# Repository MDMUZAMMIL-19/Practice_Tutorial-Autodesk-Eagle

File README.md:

# Practice_Tutorial-Autodesk-Eagle
This repository contains a collection of PCB design projects that I have completed as part of my learning journey using softwares like Autodesk Eagle, Fusion360 and EasyEDA. These projects are based on various tutorials I followed to learn PCB Design.

This repository includes the following:

Project Folders: Each project has its own folder containing all relevant files.

Schematics: .sch files for schematic diagrams and their Pdf.

Board Layouts: .brd files for PCB layouts and their Pdf.

Gerber Files: Generated Gerber files for manufacturing.

Bill of Materials (BOM): Lists of components used in each project.

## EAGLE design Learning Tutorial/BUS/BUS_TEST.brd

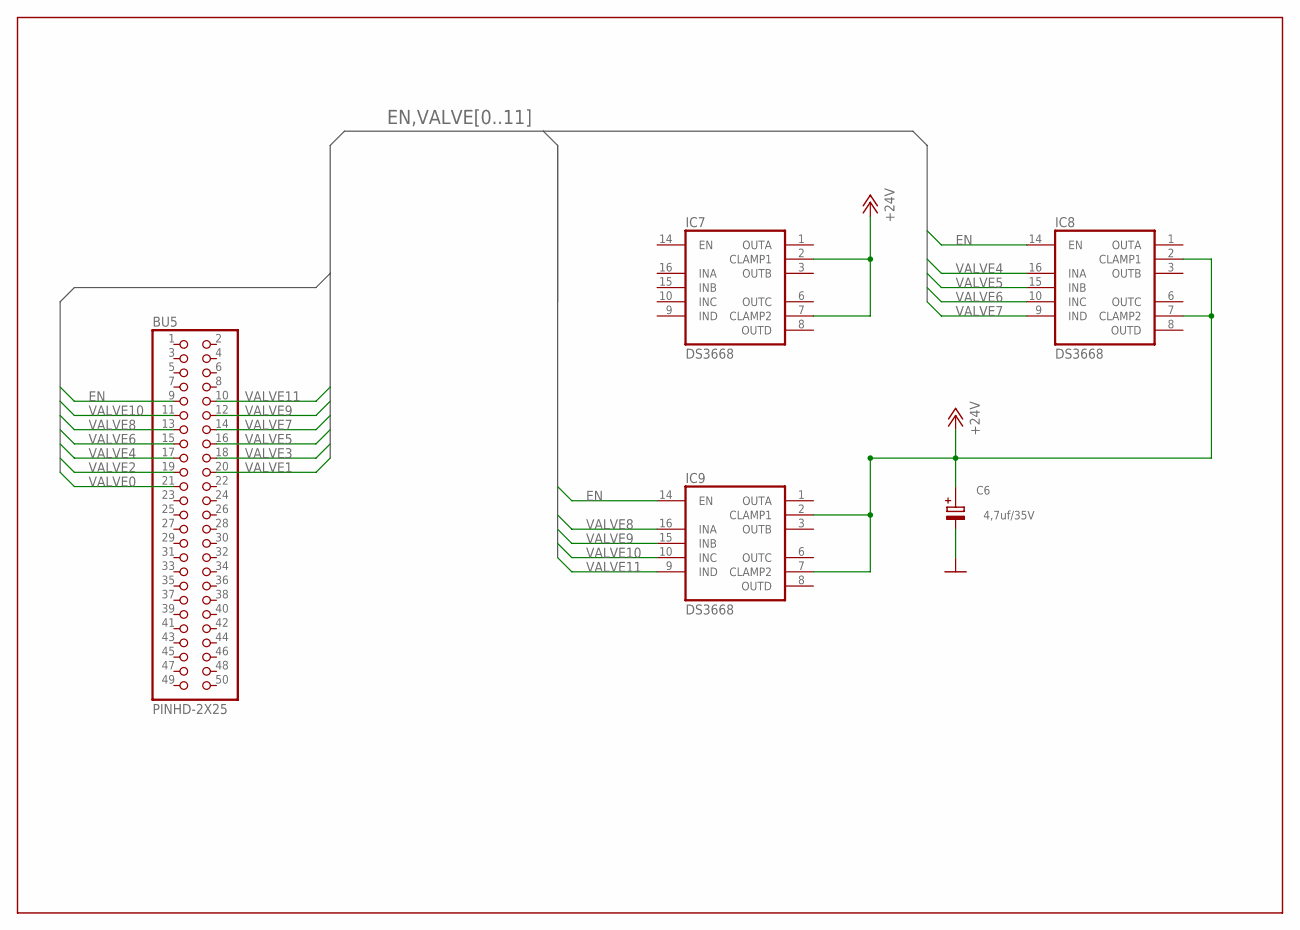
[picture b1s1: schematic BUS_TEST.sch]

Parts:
BU5: PINHD-2X25; 2X25
C6: 4,7uf/35V; E2,5-5
IC7, IC8, IC9: DS3668; DIL-16

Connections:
+24V: C6.+, IC7.2 (CLAMP1), IC7.7 (CLAMP2), IC8.2 (CLAMP1), IC8.7 (CLAMP2), IC9.2 (CLAMP1), IC9.7 (CLAMP2)
EN: BU5.9, IC8.14 (EN), IC9.14 (EN)
GND: C6.-
VALVE0: BU5.21
VALVE1: BU5.20
VALVE2: BU5.19
VALVE3: BU5.18
VALVE4: BU5.17, IC8.16 (INA)
VALVE5: BU5.16, IC8.15 (INB)
VALVE6: BU5.15, IC8.10 (INC)
VALVE7: BU5.14, IC8.9 (IND)
VALVE8: BU5.13, IC9.16 (INA)
VALVE9: BU5.12, IC9.15 (INB)
VALVE10: BU5.11, IC9.10 (INC)
VALVE11: BU5.10, IC9.9 (IND)
VCC: IC7.11 (VCC), IC8.11 (VCC), IC9.11 (VCC)
VSS: IC7.4 (VSS), IC7.5 (VSS), IC7.12 (VSS), IC7.13 (VSS), IC8.4 (VSS), IC8.5 (VSS), IC8.12 (VSS), IC8.13 (VSS), IC9.4 (VSS), IC9.5 (VSS), IC9.12 (VSS), IC9.13 (VSS)

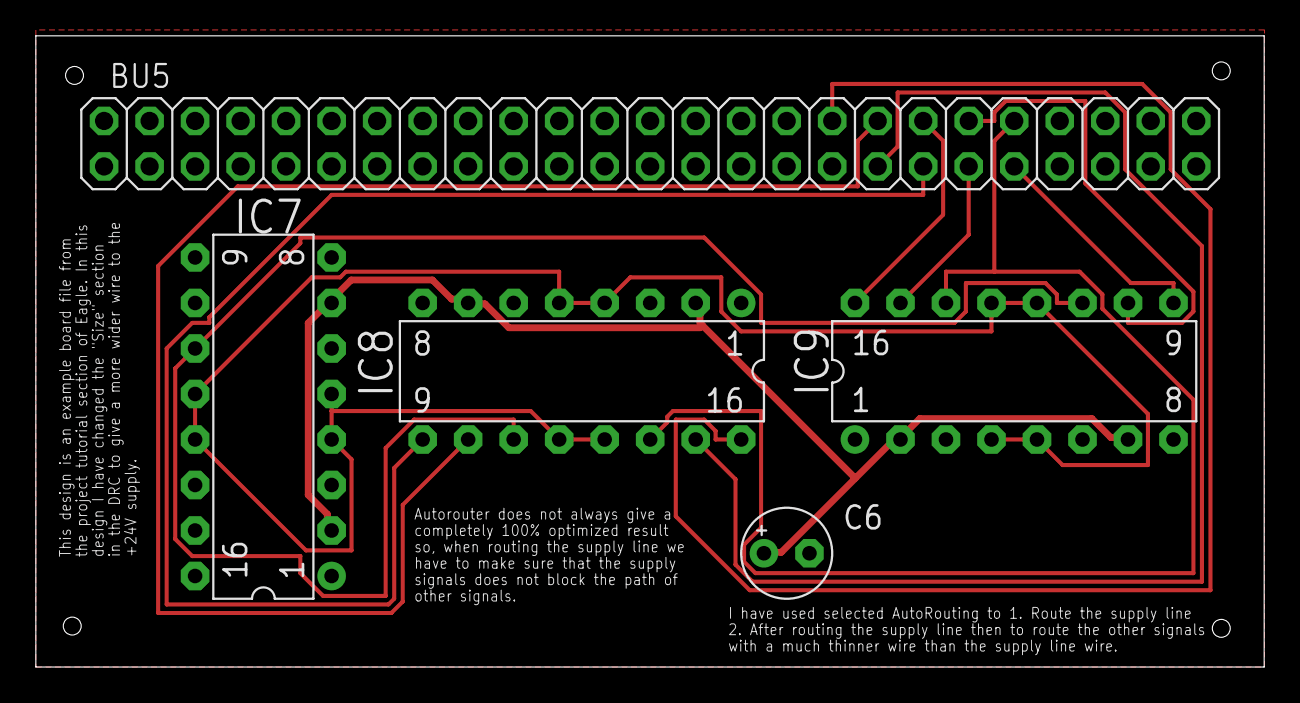
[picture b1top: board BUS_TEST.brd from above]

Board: 2 copper layers, 68.6 x 35.2 mm, 5 parts (0 on the bottom side), 12 nets.

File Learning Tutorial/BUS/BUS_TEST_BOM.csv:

Qty,Value,Device,Package,Parts
1,"4,7uf/35V",E2-5@1,"E2,5-5",C6
3,DS3668,DS3668,DIL-16,"IC7, IC8, IC9"
1,PINHD-2X25,PINHD-2X25,2X25,BU5
,,,,

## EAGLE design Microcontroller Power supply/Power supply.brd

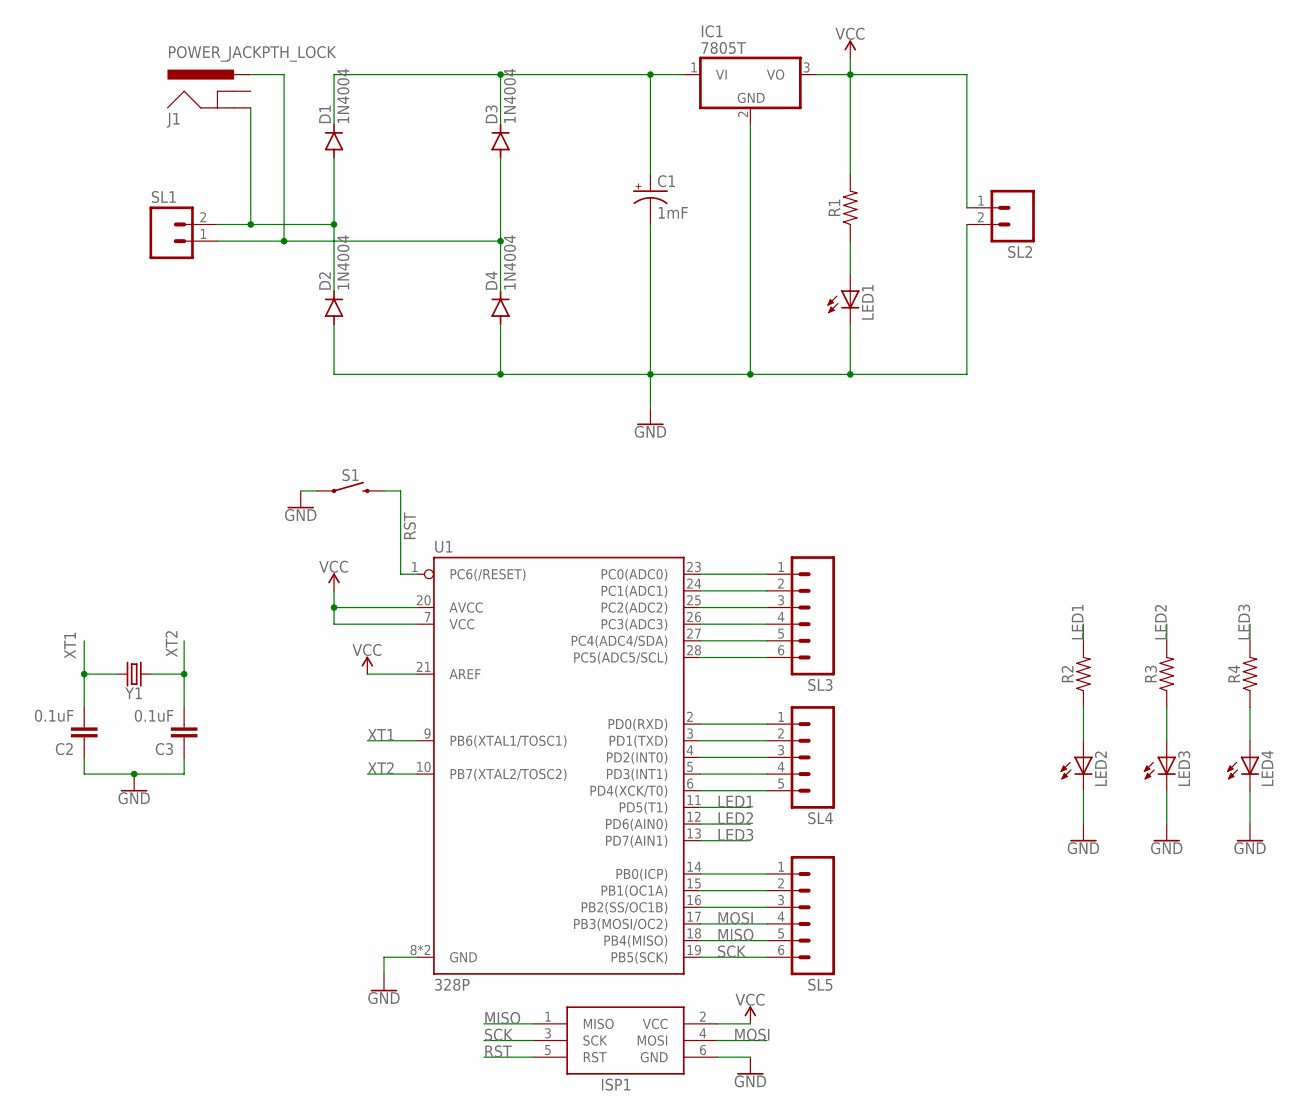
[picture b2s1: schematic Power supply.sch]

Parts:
C1: 1mF; CPOL-RADIAL-5MM-10MM
C2, C3: 0.1uF; CAP-PTH-SMALL-KIT
D1, D2, D3, D4: 1N4004; DO41-10
IC1: 7805T; TO220H
ISP1: AVRISP-6; AVRISP
J1: POWER_JACKPTH_LOCK; POWER_JACK_PTH_LOCK
LED1: LED5MM
LED2, LED3, LED4: LED3MM
R1, R2, R3, R4: AXIAL-0.3
S1: MOMENTARY-SWITCH-SPST-PTH-6.0MM; TACTILE_SWITCH_PTH_6.0MM
SL1, SL2: M02; 02P
SL3, SL5: M06; 06P
SL4: M05; 05P
U1: 328P; DIP28
Y1: CRYSTALPTH-HC49US; HC49US

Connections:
GND: C1.-, C2.1, C3.1, D2.A, D4.A, IC1.2 (GND), ISP1.6 (GND), LED1.K (C), LED2.K (C), LED3.K (C), LED4.K (C), S1.1, SL2.2, U1.8 (GND), U1.22 (GND)
LED1: R2.P$2 (2), U1.11 (PD5(T1))
LED2: R3.P$2 (2), U1.12 (PD6(AIN0))
LED3: R4.P$2 (2), U1.13 (PD7(AIN1))
MISO: ISP1.1 (MISO), SL5.5, U1.18 (PB4(MISO))
MOSI: ISP1.4 (MOSI), SL5.4, U1.17 (PB3(MOSI/OC2))
unnamed: D1.A, D2.C, J1.GND, SL1.2
unnamed: D3.A, D4.C, J1.PWR, SL1.1
unnamed: C1.+, D1.C, D3.C, IC1.1 (VI)
unnamed: LED1.A, R1.P$1 (1)
unnamed: LED4.A, R4.P$1 (1)
unnamed: LED3.A, R3.P$1 (1)
unnamed: LED2.A, R2.P$1 (1)
unnamed: SL3.1, U1.23 (PC0(ADC0))
unnamed: SL3.2, U1.24 (PC1(ADC1))
unnamed: SL3.3, U1.25 (PC2(ADC2))
unnamed: SL3.4, U1.26 (PC3(ADC3))
unnamed: SL3.5, U1.27 (PC4(ADC4/SDA))
unnamed: SL3.6, U1.28 (PC5(ADC5/SCL))
unnamed: SL4.1, U1.2 (PD0(RXD))
unnamed: SL4.2, U1.3 (PD1(TXD))
unnamed: SL4.4, U1.5 (PD3(INT1))
unnamed: SL4.5, U1.6 (PD4(XCK/T0))
unnamed: SL5.1, U1.14 (PB0(ICP))
unnamed: SL5.2, U1.15 (PB1(OC1A))
unnamed: SL5.3, U1.16 (PB2(SS/OC1B))
unnamed: SL4.3, U1.4 (PD2(INT0))
RST: ISP1.5 (RST), S1.3 (2), U1.1 (PC6(/RESET))
SCK: ISP1.3 (SCK), SL5.6, U1.19 (PB5(SCK))
VCC: IC1.3 (VO), ISP1.2 (VCC), R1.P$2 (2), SL2.1, U1.7 (VCC), U1.20 (AVCC), U1.21 (AREF)
XT1: C2.2, U1.9 (PB6(XTAL1/TOSC1)), Y1.2
XT2: C3.2, U1.10 (PB7(XTAL2/TOSC2)), Y1.1

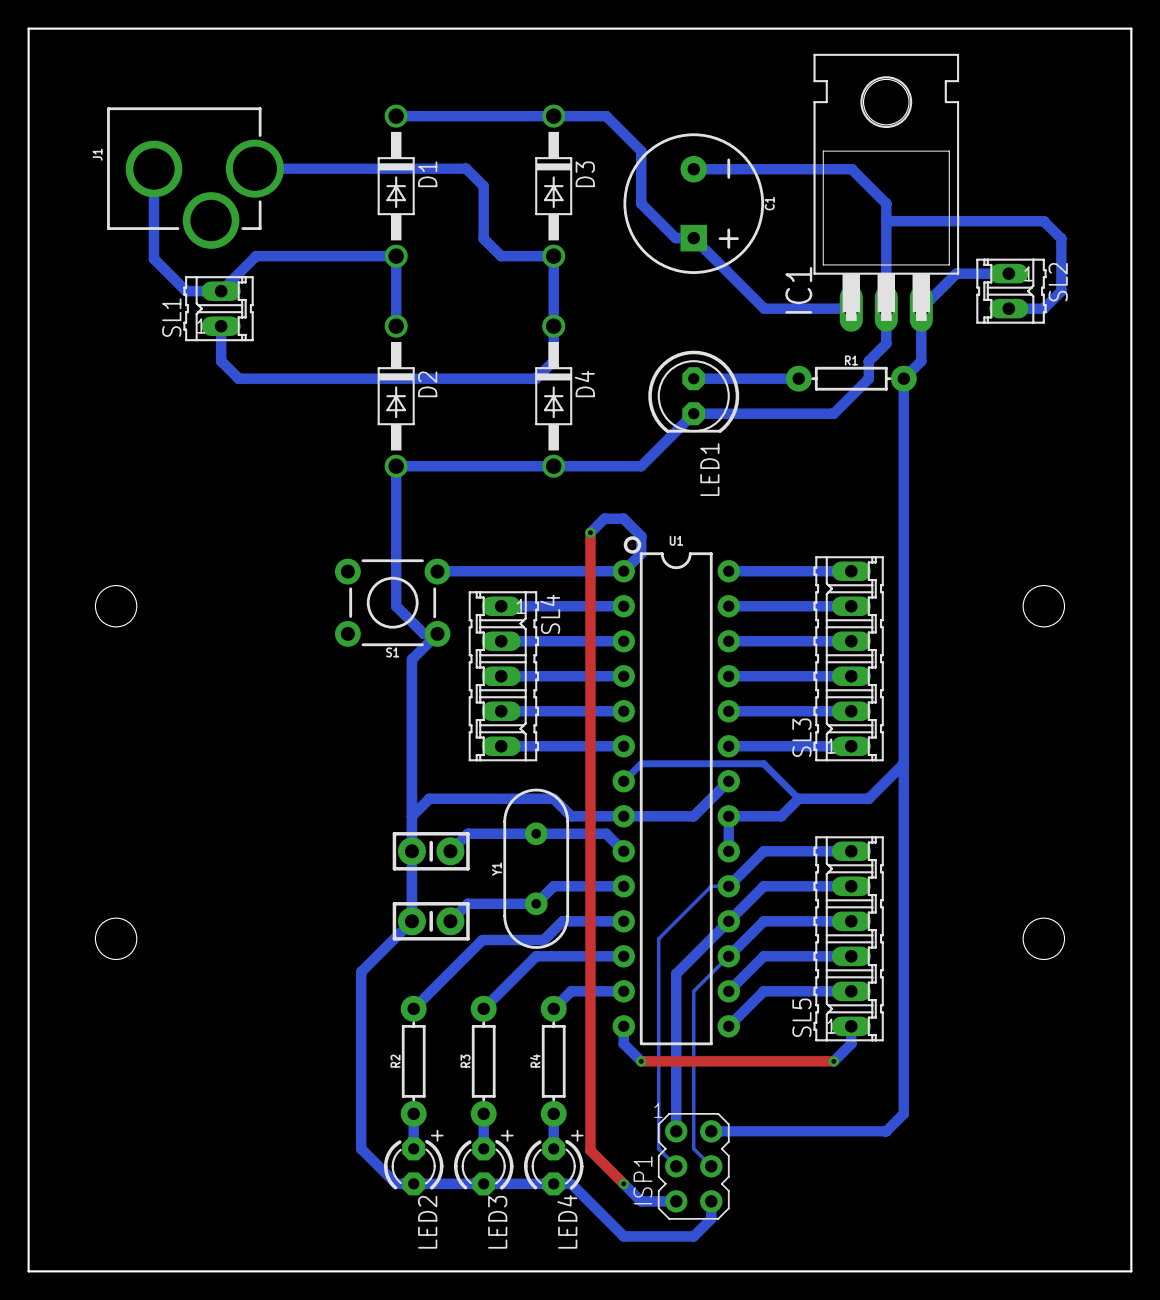
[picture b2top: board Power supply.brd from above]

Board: 2 copper layers, 80.0 x 90.2 mm, 26 parts (0 on the bottom side), 32 nets.

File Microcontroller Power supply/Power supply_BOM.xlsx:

Qty | Value | Device | Package | Parts | Description
1 |  | CRYSTALPTH-HC49US | HC49US | Y1 | Crystals (Generic)
3 |  | LED3MM | LED3MM | LED2, LED3, LED4 | LED
1 |  | LED5MM | LED5MM | LED1 | LED
2 |  | M02 | 02P | SL1, SL2 | AMP QUICK CONNECTOR
1 |  | M05 | 05P | SL4 | AMP QUICK CONNECTOR
2 |  | M06 | 06P | SL3, SL5 | AMP QUICK CONNECTOR
4 |  | RESISTORAXIAL-0.3 | AXIAL-0.3 | R1, R2, R3, R4 | Generic Resistor Package
2 | 0.1uF | 0.1UF-KIT-EZ-50V-20% | CAP-PTH-SMALL-KIT | C2, C3 | 0.1µF ceramic capacitors
4 | 1N4004 | 1N4004 | DO41-10 | D1, D2, D3, D4 | DIODE
1 | 1mF | 1000UF-RADIAL-5MM-25V-20% | CPOL-RADIAL-5MM-10MM | C1 | 1,000µF/1mF ceramic capacitors
1 | 328P | ATMEGA328P_PDIP | DIP28 | U1 | Atmel 328P
1 | 7805T | 7805T | TO220H | IC1 | Positive VOLTAGE REGULATOR
1 | AVRISP-6 | AVRISP-6 | AVRISP | ISP1 | AVR ISP HEADER
1 | MOMENTARY-SWITCH-SPST-PTH-6.0MM | MOMENTARY-SWITCH-SPST-PTH-6.0MM | TACTILE_SWITCH_PTH_6.0MM | S1 | Momentary Switch (Pushbutton) - SPST
1 | POWER_JACKPTH_LOCK | POWER_JACKPTH_LOCK | POWER_JACK_PTH_LOCK | J1 | Power Jack Connector

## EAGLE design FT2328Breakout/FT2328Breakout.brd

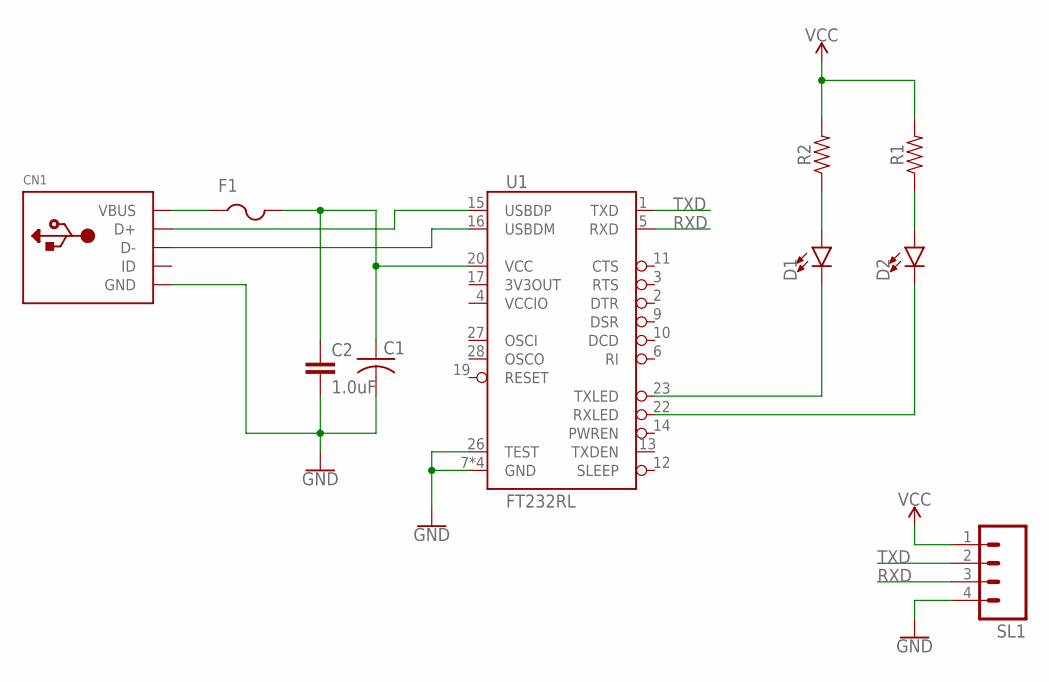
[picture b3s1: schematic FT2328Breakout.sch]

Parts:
C1: C-USC1206; C1206
C2: 1.0uF; 1206
CN1: USBMINIB; USB-MINIB
D1, D2: LED1206; LED-1206
F1: PTCFUSE-1206; R1206
R1, R2: 1206
SL1: M04; 04P
U1: FT232RL; SSOP28DB

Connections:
GND: C1.2, C2.2, CN1.GND, SL1.4, U1.7 (GND), U1.18 (GND), U1.21 (GND), U1.25 (GND), U1.26 (TEST)
unnamed: CN1.VBUS, F1.1
unnamed: C1.1, C2.1, F1.2, U1.20 (VCC)
unnamed: D1.A, R2.1
unnamed: CN1.D-, U1.16 (USBDM)
unnamed: CN1.D+, U1.15 (USBDP)
unnamed: D2.A, R1.1
unnamed: D1.C, U1.23 (TXLED)
unnamed: D2.C, U1.22 (RXLED)
RXD: SL1.3, U1.5 (RXD)
TXD: SL1.2, U1.1 (TXD)
VCC: R1.2, R2.2, SL1.1
VCCIO: U1.4 (VCCIO)

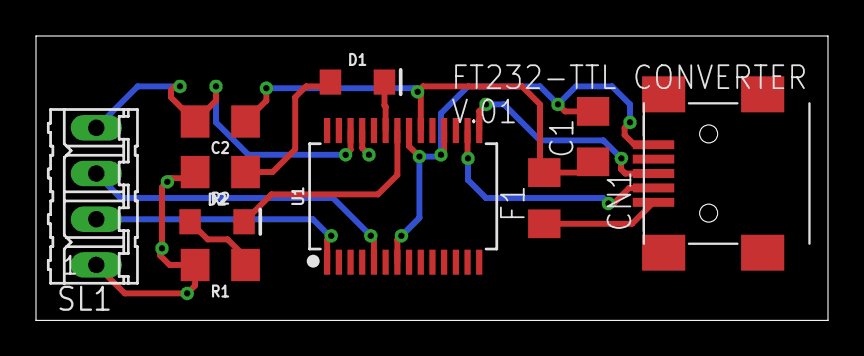
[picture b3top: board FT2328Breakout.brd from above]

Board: 2 copper layers, 44.0 x 15.8 mm, 10 parts (0 on the bottom side), 12 nets.

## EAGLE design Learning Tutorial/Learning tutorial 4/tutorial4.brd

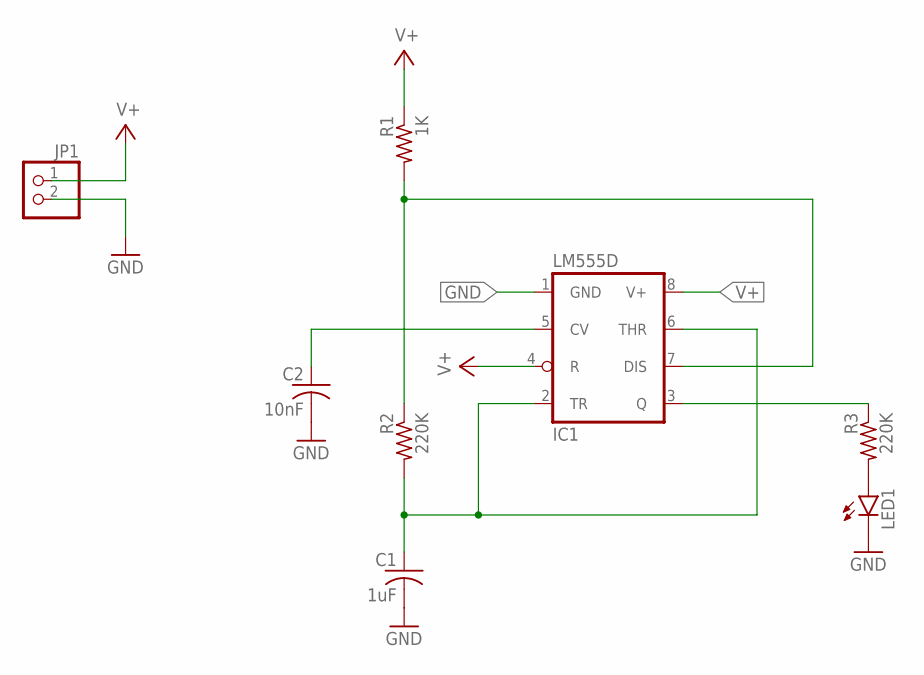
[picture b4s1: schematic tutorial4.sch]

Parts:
C1: 1uF; C0603
C2: 10nF; C0603
IC1: LM555D; SO08
JP1: PINHD-1X2; 1X02
LED1: LED5MM
R1: 1K; R0603
R2, R3: 220K; R0603

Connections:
GND: C1.2, C2.2, IC1.1 (GND), JP1.2, LED1.K (C)
unnamed: C1.1, IC1.2 (TR), IC1.6 (THR), R2.2
unnamed: IC1.7 (DIS), R1.2, R2.1
unnamed: IC1.3 (Q), R3.1
unnamed: C2.1, IC1.5 (CV)
unnamed: LED1.A, R3.2
V+: IC1.4 (R), IC1.8 (V+), JP1.1, R1.1

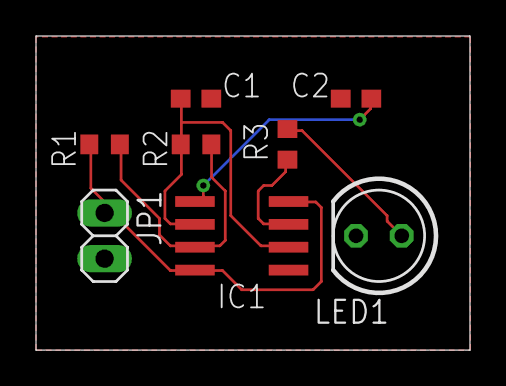
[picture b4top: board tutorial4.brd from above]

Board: 2 copper layers, 24.1 x 17.4 mm, 8 parts (0 on the bottom side), 7 nets.

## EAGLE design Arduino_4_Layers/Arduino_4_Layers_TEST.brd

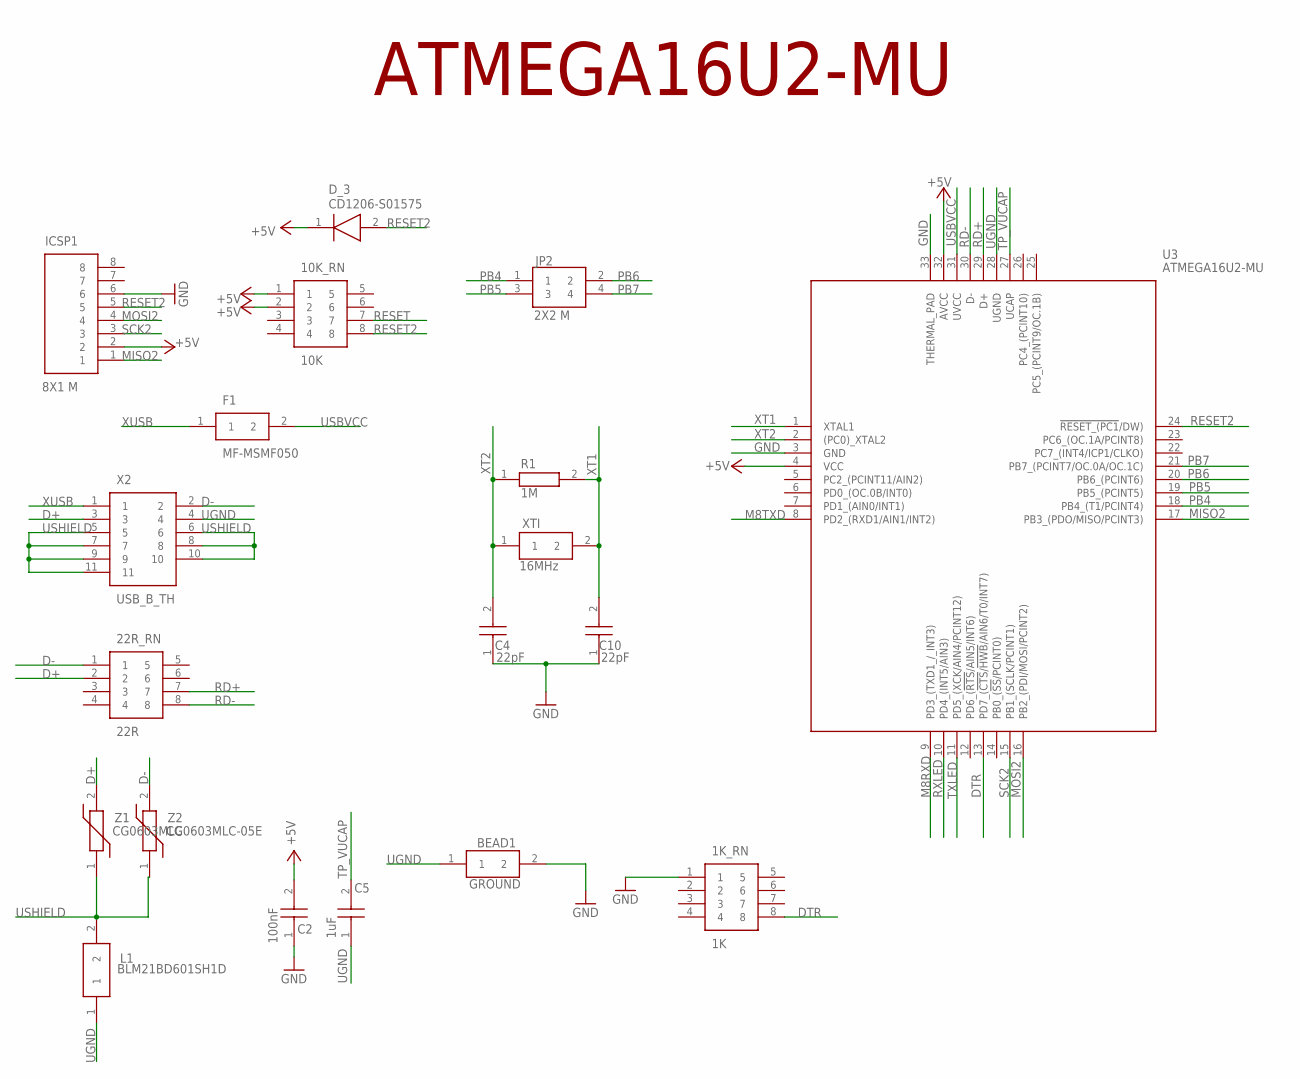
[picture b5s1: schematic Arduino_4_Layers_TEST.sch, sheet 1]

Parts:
1K_RN: 1K; CAY10-XXXJ4
10K_RN: 10K; CAY10-XXXJ4
22R_RN: 22R; CAY10-XXXJ4
BEAD1: GROUND; BEADC2012X105N
C2: 100nF; CAPC2012X130N
C4, C10: 22pF; CAPC2012X70N
C5: 1uF; CAPC2012X145N
D_3: CD1206-S01575; DIOC3016X65N
F1: MF-MSMF050; FUSC4632X75N
ICSP1: 8X1 M; HDRV8W90P0X254_1X8_2032X249X56
JP2: 2X2 M; HDRV4W77P254_2X2_467X488X821P
L1: BLM21BD601SH1D; BEADC2012X105N
R1: 1M; RESC1608X55N
U3: ATMEGA16U2-MU; QFN50P500X500X100-33N
X2: USB_B_TH; 17340351
XTI: 16MHz; MODEL-445
Z1: CG0603MLC; VARC1608X55N
Z2: CG0603MLC-05E; VARC1608X55N

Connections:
+5V: 10K_RN.1, 10K_RN.2, C2.2, D_3.1 (K), ICSP1.2, U3.4 (VCC), U3.32 (AVCC); also elsewhere on the board
D+: 22R_RN.2, X2.3, Z1.2
D-: 22R_RN.1, X2.2, Z2.2
DTR: 1K_RN.8, U3.13 (PD7_(!CTS!/!HWB!/AIN6/T0/INT7)); also elsewhere on the board
GND: 1K_RN.1, BEAD1.2, C2.1, C4.1, C10.1, ICSP1.6, U3.3 (GND), U3.33 (THERMAL_PAD); also elsewhere on the board
M8RXD: U3.9 (PD3_(TXD1_/_INT3)); also elsewhere on the board
M8TXD: U3.8 (PD2_(RXD1/AIN1/INT2)); also elsewhere on the board
MISO2: ICSP1.1, U3.17 (PB3_(PDO/MISO/PCINT3))
MOSI2: ICSP1.4, U3.16 (PB2_(PDI/MOSI/PCINT2))
PB4: JP2.1, U3.18 (PB4_(T1/PCINT4))
PB5: JP2.3, U3.19 (PB5_(PCINT5))
PB6: JP2.2, U3.20 (PB6_(PCINT6))
PB7: JP2.4, U3.21 (PB7_(PCINT7/OC.0A/OC.1C))
RD+: 22R_RN.7, U3.29 (D+)
RD-: 22R_RN.8, U3.30 (D-)
RESET: 10K_RN.7; also elsewhere on the board
RESET2: 10K_RN.8, D_3.2 (A), ICSP1.5, U3.24 (!RESET_(PC1!/DW))
RXLED: U3.10 (PD4_(INT5/AIN3)); also elsewhere on the board
SCK2: ICSP1.3, U3.15 (PB1_(SCLK/PCINT1))
TP_VUCAP: C5.2, U3.27 (UCAP)
TXLED: U3.11 (PD5_(XCK/AIN4/PCINT12)); also elsewhere on the board
UGND: BEAD1.1, C5.1, L1.1, U3.28 (UGND), X2.4
USBVCC: F1.2, U3.31 (UVCC); also elsewhere on the board
USHIELD: L1.2, X2.5, X2.6, X2.7, X2.8, X2.9, X2.10, X2.11, Z1.1, Z2.1
XT1: C10.2, R1.2, U3.1 (XTAL1), XTI.2
XT2: C4.2, R1.1, U3.2 ((PC0)_XTAL2), XTI.1
XUSB: F1.1, X2.1

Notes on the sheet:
ATMEGA16U2-MU

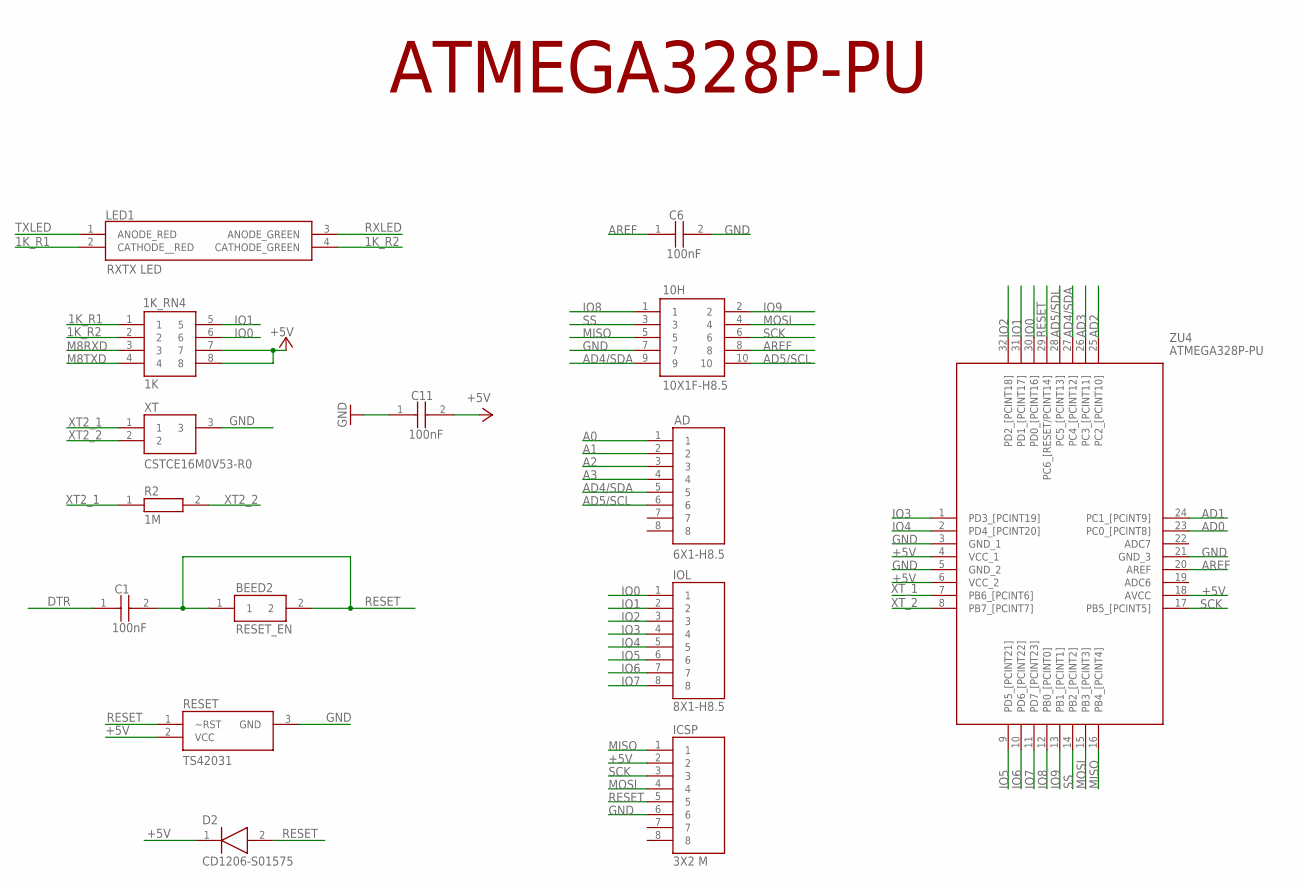
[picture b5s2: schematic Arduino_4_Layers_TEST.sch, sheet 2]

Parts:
1K_RN4: 1K; CAY10-XXXJ4
10H: 10X1F-H8.5; FTMH10503LDV
AD: 6X1-H8.5; HDRV8W90P0X254_1X8_2032X249X56
BEED2: RESET_EN; BEADC2012X105N
C1, C6, C11: 100nF; CAPC2012X130N
D2: CD1206-S01575; DIOC3016X65N
ICSP: 3X2 M; HDRV8W90P0X254_1X8_2032X249X56
IOL: 8X1-H8.5; HDRV8W90P0X254_1X8_2032X249X56
LED1: RXTX LED; SML522MD8WT86
R2: 1M; RESC1608X55N
RESET: TS42031; SOT95P240X110-3N
XT: CSTCE16M0V53-R0; CSTCE-V
ZU4: ATMEGA328P-PU; QFP80P900X900X120-32N

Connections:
1K_R1: 1K_RN4.1, LED1.2 (CATHODE__RED)
1K_R2: 1K_RN4.2, LED1.4 (CATHODE_GREEN)
+5V: 1K_RN4.7, 1K_RN4.8, C11.2, D2.1 (K), ICSP.2, RESET.2 (VCC), ZU4.4 (VCC_1), ZU4.6 (VCC_2), ZU4.18 (AVCC); also elsewhere on the board
A0: AD.1
A1: AD.2
A2: AD.3
A3: AD.4
AD0: ZU4.23 (PC0_[PCINT8])
AD1: ZU4.24 (PC1_[PCINT9])
AD2: ZU4.25 (PC2_[PCINT10])
AD3: ZU4.26 (PC3_[PCINT11])
AD4/SDA: 10H.9, AD.5, ZU4.27 (PC4_[PCINT12])
AD5/SCL: 10H.10, AD.6
AD5/SDL: ZU4.28 (PC5_[PCINT13])
AREF: 10H.8, C6.1, ZU4.20 (AREF)
DTR: C1.1; also elsewhere on the board
GND: 10H.7, C6.2, C11.1, ICSP.6, RESET.3 (GND), XT.3, ZU4.3 (GND_1), ZU4.5 (GND_2), ZU4.21 (GND_3); also elsewhere on the board
IO0: 1K_RN4.6, IOL.1, ZU4.30 (PD0_[PCINT16])
IO1: 1K_RN4.5, IOL.2, ZU4.31 (PD1_[PCINT17])
IO2: IOL.3, ZU4.32 (PD2_[PCINT18])
IO3: IOL.4, ZU4.1 (PD3_[PCINT19])
IO4: IOL.5, ZU4.2 (PD4_[PCINT20])
IO5: IOL.6, ZU4.9 (PD5_[PCINT21])
IO6: IOL.7, ZU4.10 (PD6_[PCINT22])
IO7: IOL.8, ZU4.11 (PD7_[PCINT23])
IO8: 10H.1, ZU4.12 (PB0_[PCINT0])
IO9: 10H.2, ZU4.13 (PB1_[PCINT1])
M8RXD: 1K_RN4.3; also elsewhere on the board
M8TXD: 1K_RN4.4; also elsewhere on the board
MISO: 10H.5, ICSP.1, ZU4.16 (PB4_[PCINT4])
MOSI: 10H.4, ICSP.4, ZU4.15 (PB3_[PCINT3])
RESET: BEED2.1, BEED2.2, C1.2, D2.2 (A), ICSP.5, RESET.1 (~RST), ZU4.29 (PC6_[RESET/PCINT14]); also elsewhere on the board
RXLED: LED1.3 (ANODE_GREEN); also elsewhere on the board
SCK: 10H.6, ICSP.3, ZU4.17 (PB5_[PCINT5]); also elsewhere on the board
SS: 10H.3, ZU4.14 (PB2_[PCINT2])
TXLED: LED1.1 (ANODE_RED); also elsewhere on the board
XT2_1: R2.1, XT.1
XT2_2: R2.2, XT.2
XT_1: ZU4.7 (PB6_[PCINT6])
XT_2: ZU4.8 (PB7_[PCINT7])

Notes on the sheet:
ATMEGA328P-PU

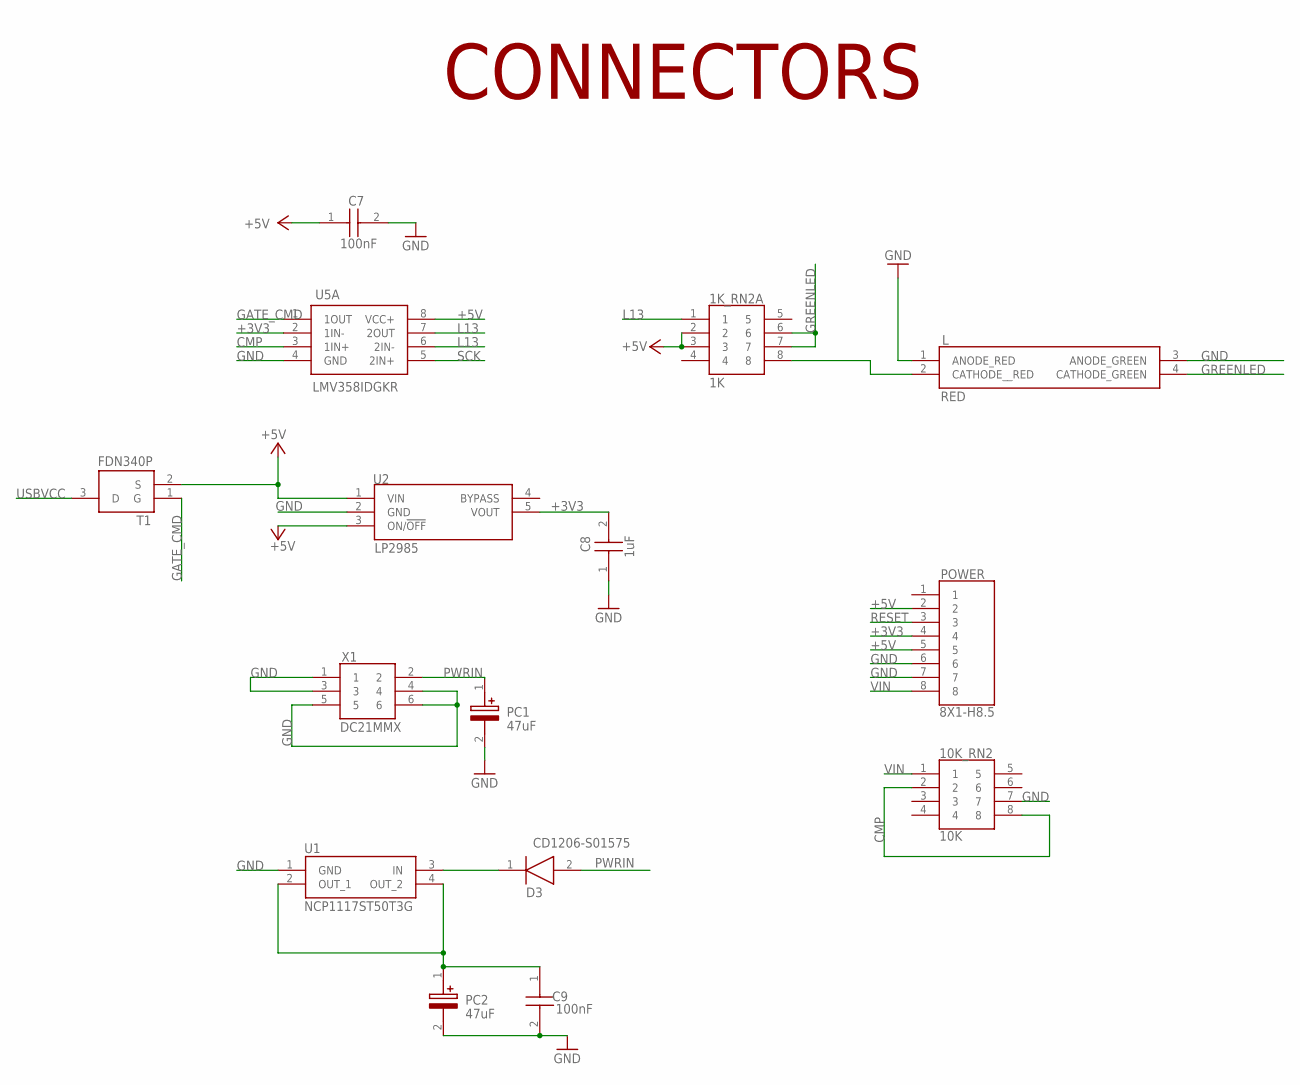
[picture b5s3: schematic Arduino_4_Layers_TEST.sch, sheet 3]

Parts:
1K_RN2A: 1K; CAY10-XXXJ4
10K_RN2: 10K; CAY10-XXXJ4
C7, C9: 100nF; CAPC2012X130N
C8: 1uF; CAPC2012X145N
D3: CD1206-S01575; DIOC3016X65N
L: RED; SML522MD8WT86
PC1, PC2: 47uF; CAPAE530X610N
POWER: 8X1-H8.5; HDRV8W90P0X254_1X8_2032X249X56
T1: FDN340P; SOT95P251X112-3N
U1: NCP1117ST50T3G; SOT230P700X180-4N
U2: LP2985; SOT95P280X145-5N
U5A: LMV358IDGKR; SOP65P490X110-8N
X1: DC21MMX; USBBSRA

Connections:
+3V3: C8.2, POWER.4, U2.5 (VOUT), U5A.2 (1IN-)
+5V: 1K_RN2A.2, 1K_RN2A.3, C7.1, POWER.2, POWER.5, T1.2 (S), U2.1 (VIN), U2.3 (ON/!OFF), U5A.8 (VCC+); also elsewhere on the board
CMP: 10K_RN2.2, 10K_RN2.8, U5A.3 (1IN+)
GATE_CMD: T1.1 (G), U5A.1 (1OUT)
GND: 10K_RN2.7, C7.2, C8.1, C9.2, L.1 (ANODE_RED), L.3 (ANODE_GREEN), PC1.2 (-), PC2.2 (-), POWER.6, POWER.7, U1.1 (GND), U2.2 (GND), U5A.4 (GND), X1.1, X1.3, X1.4, X1.5, X1.6; also elsewhere on the board
GREENLED: 1K_RN2A.6, 1K_RN2A.7, L.4 (CATHODE_GREEN)
L13: 1K_RN2A.1, U5A.6 (2IN-), U5A.7 (2OUT)
unnamed: 1K_RN2A.8, L.2 (CATHODE__RED)
unnamed: D3.1 (K), U1.3 (IN)
unnamed: C9.1, PC2.1 (+), U1.2 (OUT_1), U1.4 (OUT_2)
PWRIN: D3.2 (A), PC1.1 (+), X1.2
RESET: POWER.3; also elsewhere on the board
SCK: U5A.5 (2IN+); also elsewhere on the board
USBVCC: T1.3 (D); also elsewhere on the board
VIN: 10K_RN2.1, POWER.8

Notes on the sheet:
CONNECTORS

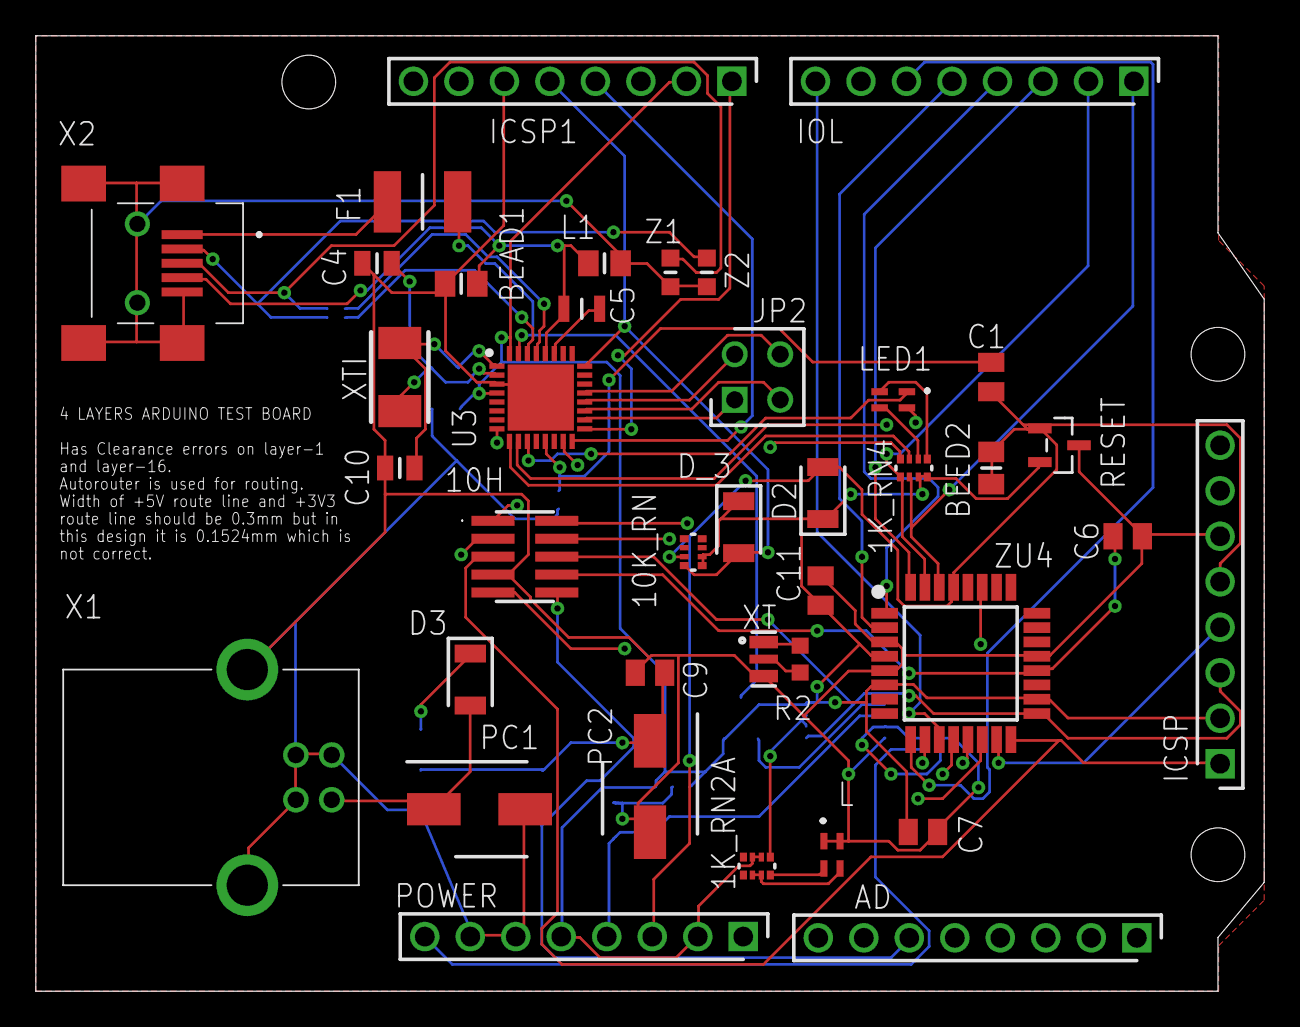
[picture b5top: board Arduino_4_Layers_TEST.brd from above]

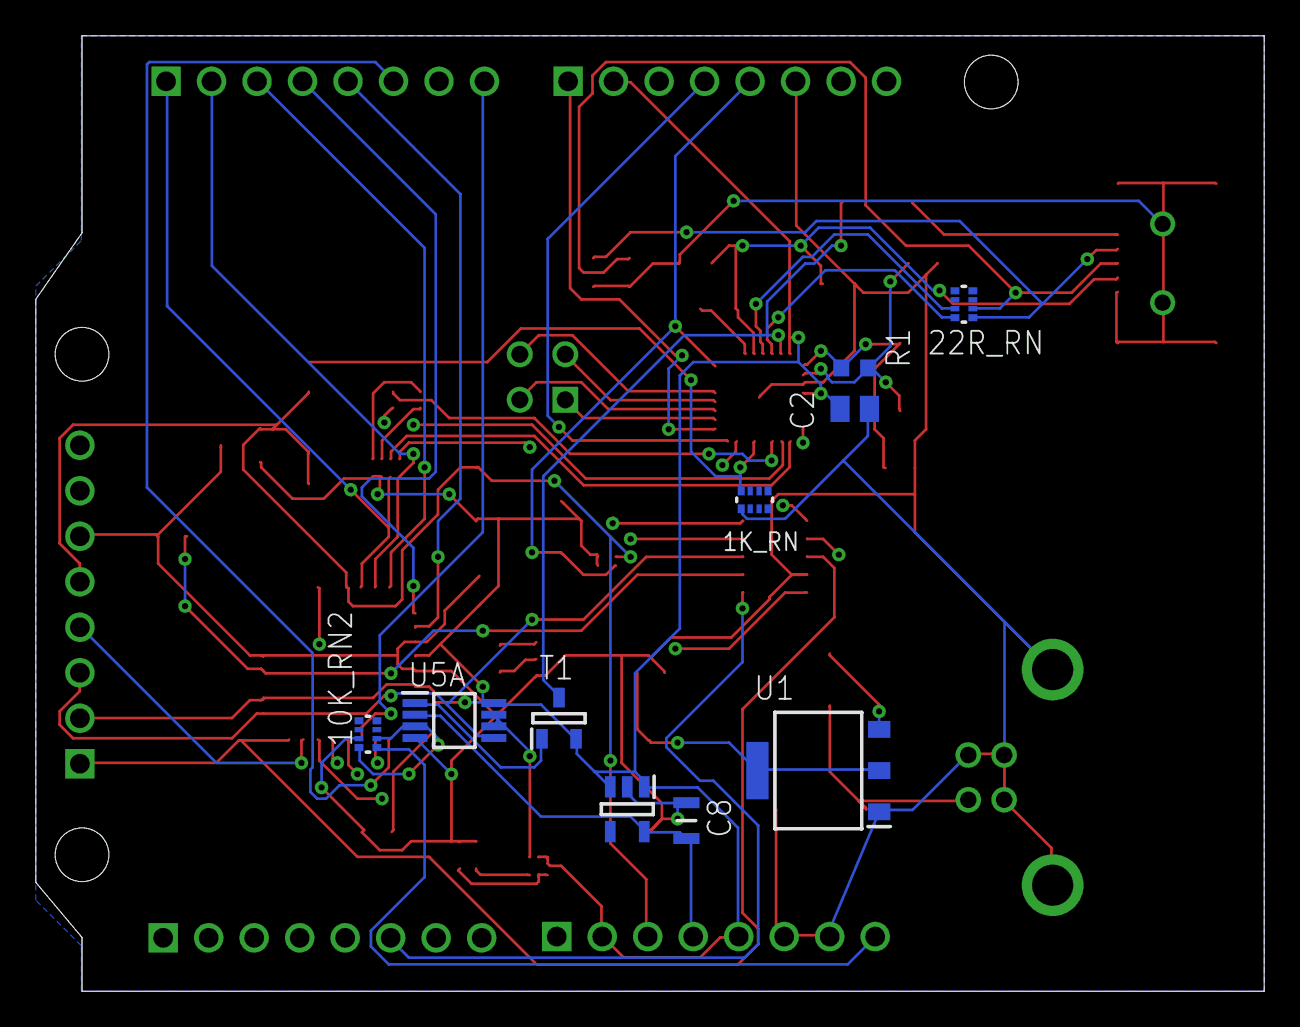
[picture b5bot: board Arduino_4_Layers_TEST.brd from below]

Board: 4 copper layers, 68.6 x 53.3 mm, 49 parts (10 on the bottom side), 58 nets.

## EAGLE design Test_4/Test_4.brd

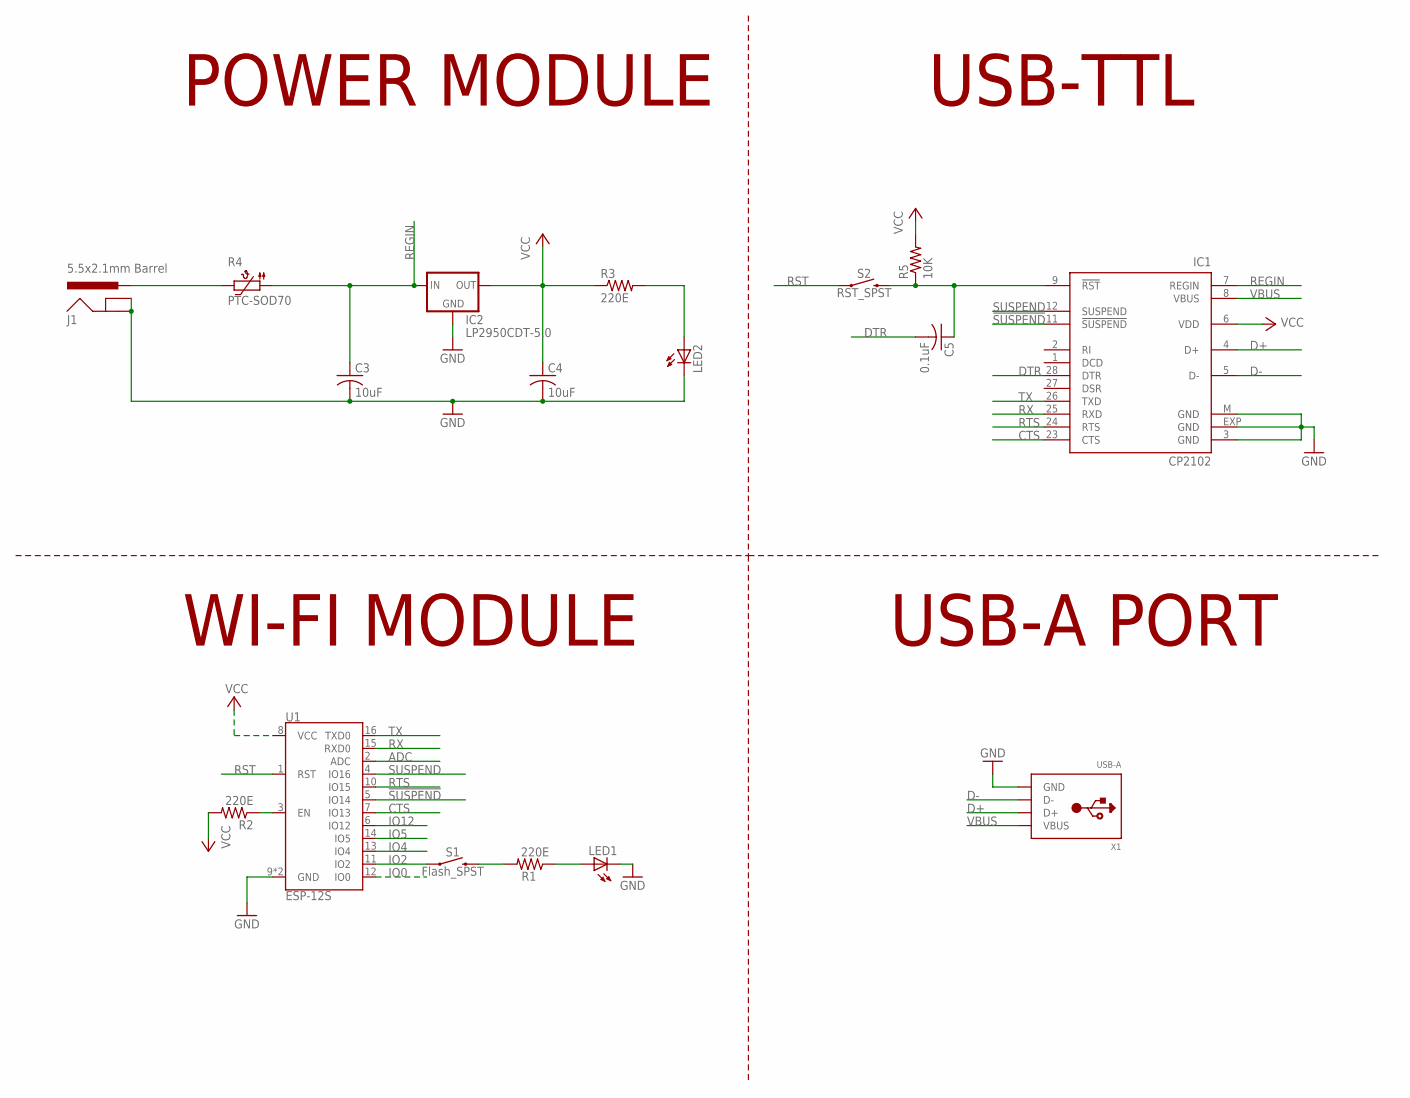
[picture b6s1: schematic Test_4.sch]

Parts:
C3, C4: 10uF; C0805
C5: 0.1uF; C0805
IC1: CP2102; MLP28
IC2: LP2950CDT-5.0; DPACK
J1: 5.5x2.1mm Barrel; POWER_JACK_SMD
LED1, LED2: LEDCHIPLED_0805; CHIPLED_0805
R1, R2, R3: 220E; R0805
R4: PTC-SOD70; SOD70
R5: 10K; R0805
S1: Flash_SPST; TACTILE_SWITCH_SMD_5.2MM
S2: RST_SPST; TACTILE_SWITCH_SMD_5.2MM
U1: ESP-12S
X1: USB-A; MOLEX_480371000

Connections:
!SUSPEND: IC1.11 (!SUSPEND), U1.5 (IO14)
+5V: C4.1, IC1.6 (VDD), IC2.3 (OUT), R2.2, R3.1, R5.2
ADC: U1.2 (ADC)
CTS: IC1.23 (CTS), U1.7 (IO13)
D+: IC1.4 (D+), X1.3 (D+)
D-: IC1.5 (D-), X1.2 (D-)
DTR: C5.2, IC1.28 (DTR)
GND: C3.2, C4.2, IC2.4 (GND), J1.GND (GNDBREAK), J1.P$4 (GND), LED1.C, LED2.C, U1.9 (GND), U1.P$1 (GND), X1.4 (GND)
IO0: U1.12 (IO0)
IO2: S1.1, S1.2 (1), U1.11 (IO2)
IO4: U1.13 (IO4)
IO5: U1.14 (IO5)
IO12: U1.6 (IO12)
unnamed: LED1.A, R1.1
unnamed: IC1.3 (GND), IC1.EXP (GND), IC1.M (GND)
unnamed: R1.2, S1.3 (2), S1.4 (2)
unnamed: J1.VIN0 (PWR), R4.2
unnamed: LED2.A, R3.2
unnamed: C5.1, IC1.9 (!RST), R5.1, S2.3 (2), S2.4 (2)
unnamed: R2.1, U1.3 (EN)
REGIN: C3.1, IC1.7 (REGIN), IC2.1 (IN), R4.1
RST: S2.1, S2.2 (1), U1.1 (RST)
RTS: IC1.24 (RTS), U1.10 (IO15)
RX: IC1.25 (RXD), U1.15 (RXD0)
SUSPEND: IC1.12 (SUSPEND), U1.4 (IO16)
TX: IC1.26 (TXD), U1.16 (TXD0)
VBUS: IC1.8 (VBUS), X1.1 (VBUS)
VCC: U1.8 (VCC)

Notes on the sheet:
POWER MODULE
USB-TTL
WI-FI MODULE
USB-A PORT

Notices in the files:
parts and their libraries:
SparkFun-Capacitors: Licensing: Creative Commons ShareAlike 4.0 International - https://creativecommons.org/licenses/by-sa/4.0
